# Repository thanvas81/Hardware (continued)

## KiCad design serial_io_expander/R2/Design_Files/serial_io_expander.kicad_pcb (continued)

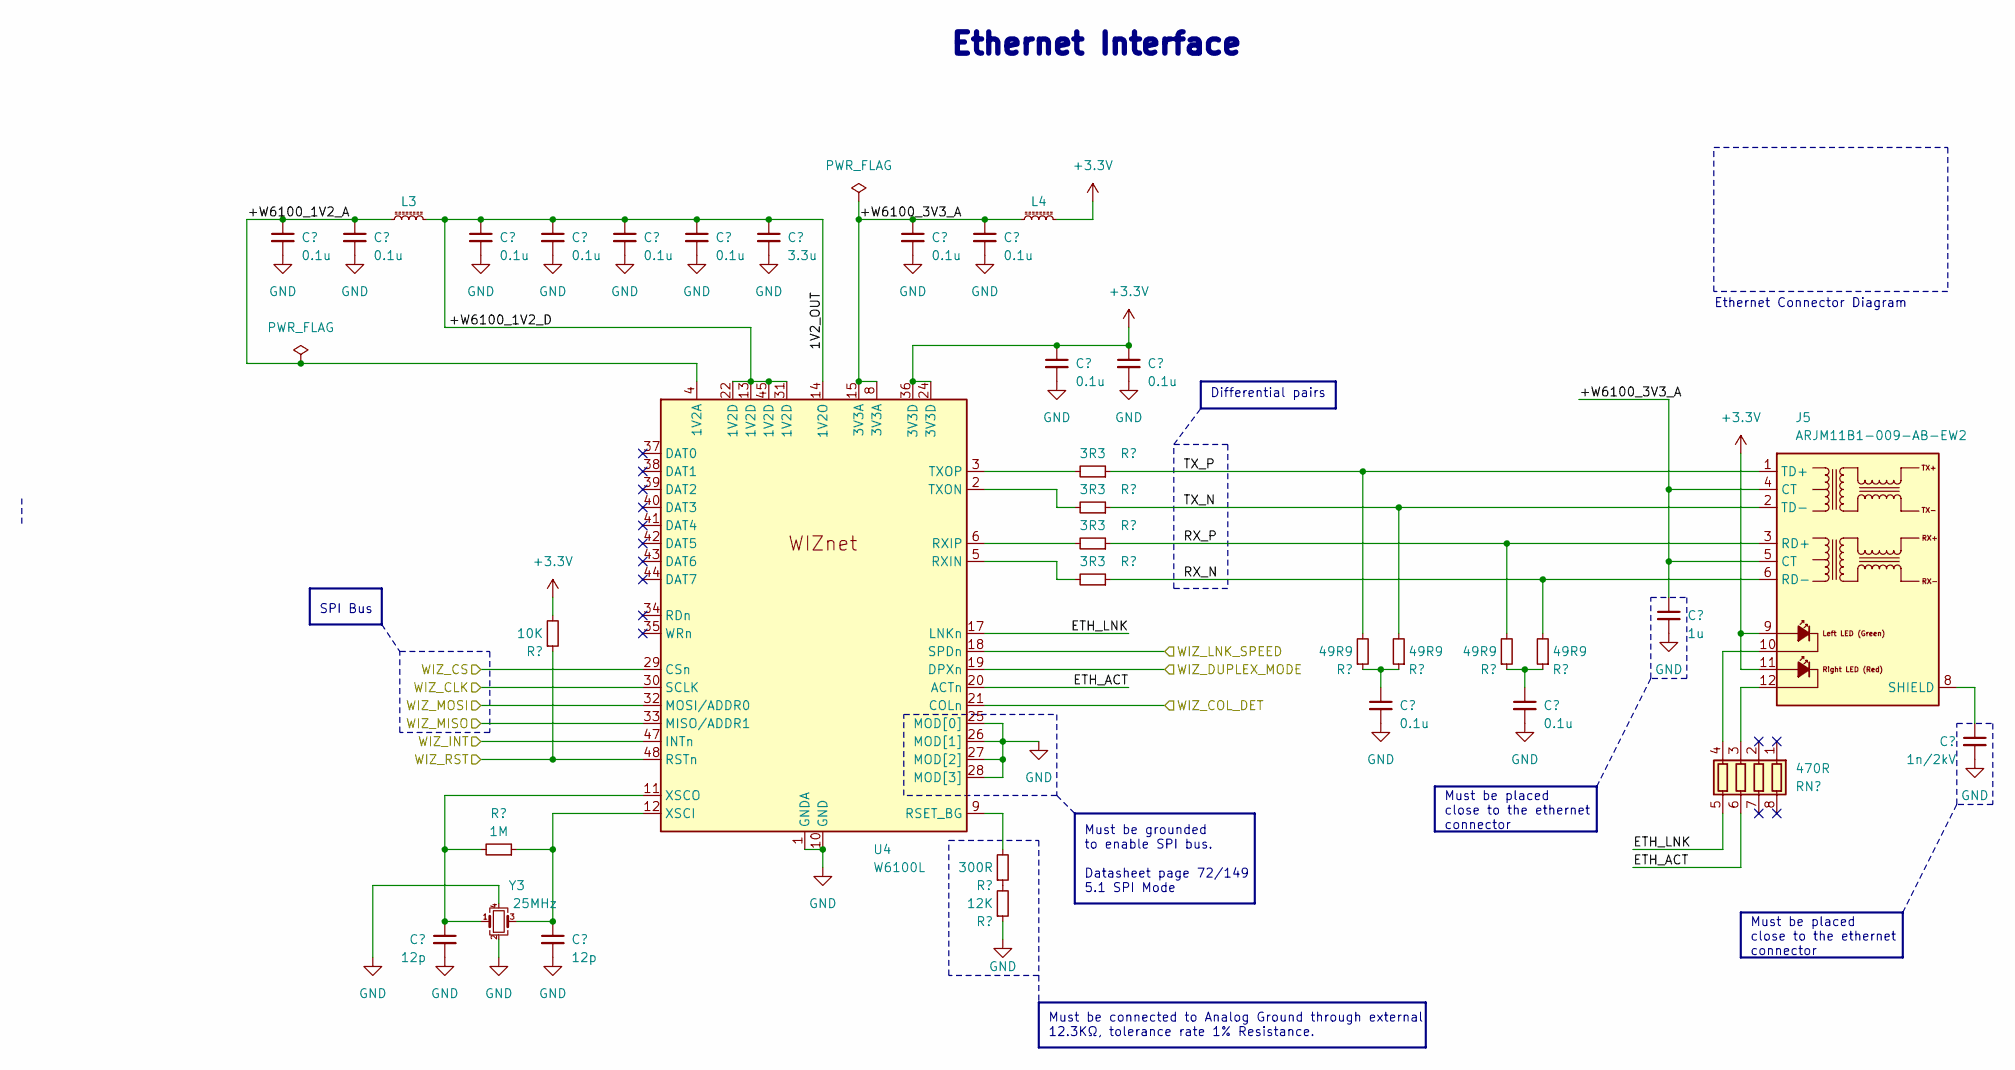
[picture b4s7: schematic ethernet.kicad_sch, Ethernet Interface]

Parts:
C31, C32, C34, C35, C37, C38, C40, C41, C42, C43, C44, C45: 0.1u; C_0603_1608Metric; PartkeeprID 50
C33, C36: 12p; C_0603_1608Metric; PartkeeprID 50
C39: 3.3u; C_0603_1608Metric
C46: 1u; C_0805_2012Metric; PartkeeprID 50
C47: 1n/2kV; C_1206_3216Metric; PartkeeprID 50
J5: ARJM11B1-009-AB-EW2; ARJM11B1-009-AB-EW2_Horizontal
L3, L4: L_Ferrite_Small; L_0603_1608Metric
R79: 1M; R_0402_1005Metric
R80: 10K; R_0603_1608Metric
R81: 300R; R_0402_1005Metric
R82: 12K; R_0402_1005Metric
R83, R84, R85, R86: 3R3; R_0402_1005Metric
R87, R88, R89, R90: 49R9; R_0402_1005Metric
RN1: 470R; R_Array_Concave_4x0603
U4: W6100L; LQFP-48_7x7mm_P0.5mm
Y3: 25MHz; Crystal_SMD_3225-4Pin_3.2x2.5mm

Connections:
/Ethernet/+W6100_1V2_A: C31.1, C32.1, L3.2, U4.4 (1V2A)
/Ethernet/+W6100_1V2_D: C34.1, C35.1, C37.1, C38.1, C39.1, L3.1, U4.13 (1V2D), U4.14 (1V2O), U4.22 (1V2D), U4.31 (1V2D), U4.45 (1V2D)
/Ethernet/+W6100_3V3_A: C40.1, C41.1, C46.1, J5.4 (CT), J5.5 (CT), L4.1, U4.8 (3V3A), U4.15 (3V3A)
/Ethernet/RX_N: J5.6 (RD-), R86.1, R90.2
/Ethernet/RX_P: J5.3 (RD+), R85.1, R89.2
/Ethernet/TX_N: J5.2 (TD-), R84.1, R88.2
/Ethernet/TX_P: J5.1 (TD+), R83.1, R87.2
/Ethernet/WIZ_CLK: U4.30 (SCLK); also elsewhere on the board
/Ethernet/WIZ_COL_DET: U4.21 (COLn); also elsewhere on the board
/Ethernet/WIZ_CS: U4.29 (CSn); also elsewhere on the board
/Ethernet/WIZ_DUPLEX_MODE: U4.19 (DPXn); also elsewhere on the board
/Ethernet/WIZ_INT: U4.47 (INTn); also elsewhere on the board
/Ethernet/WIZ_LNK_SPEED: U4.18 (SPDn); also elsewhere on the board
/Ethernet/WIZ_MISO: U4.33 (MISO/ADDR1); also elsewhere on the board
/Ethernet/WIZ_MOSI: U4.32 (MOSI/ADDR0); also elsewhere on the board
/Ethernet/WIZ_RST: R80.1, U4.48 (RSTn); also elsewhere on the board
GND: C31.2, C32.2, C33.2, C34.2, C35.2, C36.2, C37.2, C38.2, C39.2, C40.2, C41.2, C42.2, C43.2, C44.2, C45.2, C46.2, C47.2, R82.1, U4.1 (GNDA), U4.7 (GNDA), U4.10 (GND), U4.16 (GNDA), U4.23 (GND), U4.25 (MOD[0]), U4.26 (MOD[1]), U4.27 (MOD[2]), U4.28 (MOD[3]), U4.46 (GND), Y3.2, Y3.4; also elsewhere on the board
unnamed: C44.1, R87.1, R88.1
unnamed: C45.1, R89.1, R90.1
unnamed: C47.1, J5.8 (SHIELD)
unnamed: R81.1, R82.2
unnamed: R81.2, U4.9 (RSET_BG)
unnamed: R86.2, U4.5 (RXIN)
unnamed: R85.2, U4.6 (RXIP)
unnamed: R84.2, U4.2 (TXON)
unnamed: R83.2, U4.3 (TXOP)
unnamed: C36.1, R79.1, U4.12 (XSCI), Y3.3
unnamed: C33.1, R79.2, U4.11 (XSCO), Y3.1

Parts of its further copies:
RN8: 470R; R_Array_Concave_4x0603

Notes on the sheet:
${TITLE}
Must be connected to Analog Ground through external 12.3KΩ, tolerance rate 1% Resistance.
Must be placed close to the ethernet connector
SPI Bus
Must be grounded to enable SPI bus. Datasheet page 72/149 5.1 SPI Mode
Differential pairs
Ethernet Connector Diagram

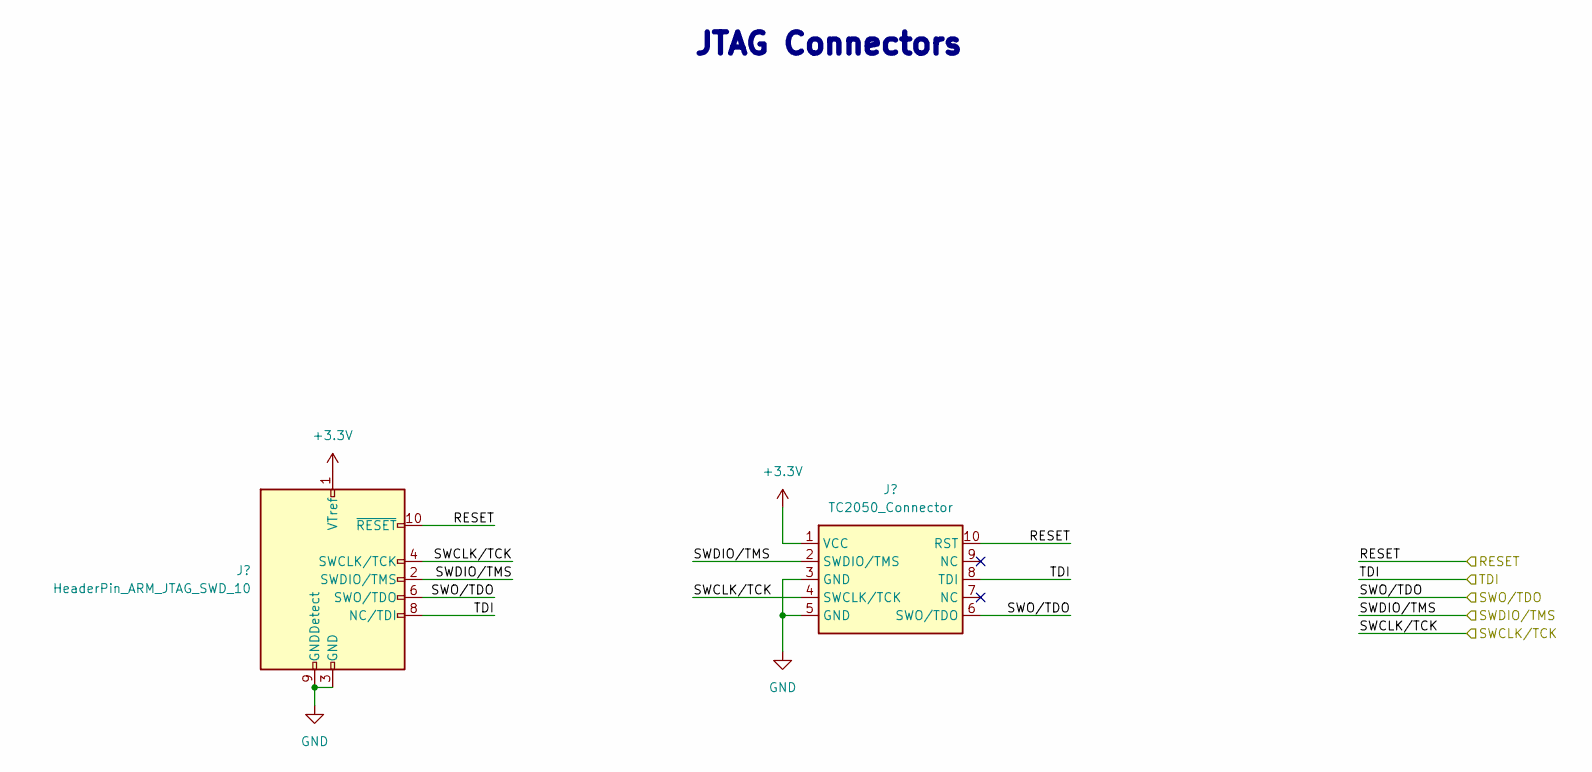
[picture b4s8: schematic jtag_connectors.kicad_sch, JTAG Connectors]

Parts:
J6: HeaderPin_ARM_JTAG_SWD_10; PinHeader_2x05_P2.54mm_Vertical
J7: TC2050_Connector; Tag-Connect_TC2050-IDC-NL_2x05_P1.27mm_Vertical

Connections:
/mcu/RESET: J6.10 (~RESET), J7.10 (RST); also elsewhere on the board
/mcu/SWCLK/TCK: J6.4 (SWCLK/TCK), J7.4 (SWCLK/TCK); also elsewhere on the board
/mcu/SWDIO/TMS: J6.2 (SWDIO/TMS), J7.2 (SWDIO/TMS); also elsewhere on the board
/mcu/SWO/TDO: J6.6 (SWO/TDO), J7.6 (SWO/TDO); also elsewhere on the board
/mcu/TDI: J6.8 (NC/TDI), J7.8 (TDI); also elsewhere on the board
GND: J6.3 (GND), J6.5 (GND), J6.9 (GNDDetect), J7.3 (GND), J7.5 (GND); also elsewhere on the board

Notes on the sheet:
${TITLE}

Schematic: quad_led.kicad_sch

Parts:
D47, D50, D53, D56: LED_Small_Filled; LED_0603_1608Metric
RN3: R_Pack04_Split; R_Array_Concave_4x0603
U7: PUMH11,115; SOT-363_SC-70-6

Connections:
/LED indicators/LED13: U7.2; also elsewhere on the board
/LED indicators/LED14: U7.5; also elsewhere on the board
GND: U7.1, U7.4; also elsewhere on the board

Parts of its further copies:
D24, D25, D26, D27, D28, D29, D30, D31, D32, D33, D34, D35, D36, D37, D38, D39, D40, D41, D42, D43, D48, D49: LED_Small_Filled; LED_0603_1608Metric
RN4, RN5, RN6, RN7, RN19: R_Pack04_Split; R_Array_Concave_4x0603
U8, U9, U10, U11, U12, U13, U14, U17, U18, U19, U20: PUMH11,115; SOT-363_SC-70-6

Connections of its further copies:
/LED indicators/LED1: U19.2; also elsewhere on the board
/LED indicators/LED2: U19.5; also elsewhere on the board
/LED indicators/LED3: U20.2; also elsewhere on the board
/LED indicators/LED4: U20.5; also elsewhere on the board
/LED indicators/LED5: U8.2; also elsewhere on the board
/LED indicators/LED6: U8.5; also elsewhere on the board
/LED indicators/LED7: U9.2; also elsewhere on the board
/LED indicators/LED8: U9.5; also elsewhere on the board
/LED indicators/LED9: U11.2; also elsewhere on the board
/LED indicators/LED10: U11.5; also elsewhere on the board
/LED indicators/LED11: U12.2; also elsewhere on the board
/LED indicators/LED12: U12.5; also elsewhere on the board
/LED indicators/LED15: U10.2; also elsewhere on the board
/LED indicators/LED16: U10.5; also elsewhere on the board
/LED indicators/LED17: U13.2; also elsewhere on the board
/LED indicators/LED18: U13.5; also elsewhere on the board
/LED indicators/LED19: U14.2; also elsewhere on the board
/LED indicators/LED20: U14.5; also elsewhere on the board
/LED indicators/LED21: U17.2; also elsewhere on the board
/LED indicators/LED22: U17.5; also elsewhere on the board
/LED indicators/LED23: U18.2; also elsewhere on the board
/LED indicators/LED24: U18.5; also elsewhere on the board
GND: U8.1, U8.4, U9.1, U9.4, U10.1, U10.4, U11.1, U11.4, U12.1, U12.4, U13.1, U13.4, U14.1, U14.4, U17.1, U17.4, U18.1, U18.4, U19.1, U19.4, U20.1, U20.4; also elsewhere on the board
unnamed: D24.1 (K), RN19.1 (R1.1)
unnamed: D25.1 (K), RN19.2 (R2.1)
unnamed: D32.1 (K), RN4.1 (R1.1)
unnamed: D33.1 (K), RN4.2 (R2.1)
unnamed: D34.1 (K), RN4.3 (R3.1)
unnamed: D35.1 (K), RN4.4 (R4.1)
unnamed: D36.1 (K), RN5.1 (R1.1)
unnamed: D37.1 (K), RN5.2 (R2.1)
unnamed: D38.1 (K), RN5.3 (R3.1)
unnamed: D39.1 (K), RN5.4 (R4.1)
unnamed: D40.1 (K), RN6.1 (R1.1)
unnamed: D41.1 (K), RN6.2 (R2.1)
unnamed: D42.1 (K), RN6.3 (R3.1)
unnamed: D43.1 (K), RN6.4 (R4.1)
unnamed: D48.1 (K), RN7.2 (R2.1)
unnamed: D49.1 (K), RN7.3 (R3.1)
unnamed: RN4.8 (R1.2), U11.6
unnamed: RN4.7 (R2.2), U11.3
unnamed: RN4.6 (R3.2), U12.6
unnamed: RN4.5 (R4.2), U12.3
unnamed: RN5.8 (R1.2), U13.6
unnamed: RN5.7 (R2.2), U13.3
unnamed: RN5.6 (R3.2), U14.6
unnamed: RN5.5 (R4.2), U14.3
unnamed: RN6.8 (R1.2), U17.6
unnamed: RN6.7 (R2.2), U17.3
unnamed: RN6.6 (R3.2), U18.6
unnamed: RN6.5 (R4.2), U18.3
unnamed: RN7.8 (R1.2), U19.6
unnamed: RN7.7 (R2.2), U19.3
unnamed: RN7.6 (R3.2), U20.6
unnamed: RN7.5 (R4.2), U20.3
unnamed: RN19.8 (R1.2), U8.6
unnamed: RN19.7 (R2.2), U8.3
unnamed: RN19.6 (R3.2), U9.6
unnamed: RN19.5 (R4.2), U9.3

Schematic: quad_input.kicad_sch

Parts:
D8, D13, D18, D23: TBAW56,LM; SOT-23
RN9: 120K; R_Array_Concave_4x0603
RN10: 47K; R_Array_Concave_4x0603
U5, U6: PUMH11,115; SOT-363_SC-70-6

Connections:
/digital_inputs/COLLECTOR1: U6.3; also elsewhere on the board
/digital_inputs/COLLECTOR2: U6.6; also elsewhere on the board
/digital_inputs/COLLECTOR3: U5.6; also elsewhere on the board
/digital_inputs/COLLECTOR4: U5.3; also elsewhere on the board
/digital_inputs/IN1: RN9.8 (R1.2), RN10.5 (R4.2); also elsewhere on the board
/digital_inputs/IN2: RN9.7 (R2.2), RN10.6 (R3.2); also elsewhere on the board
/digital_inputs/IN3: RN9.6 (R3.2), RN10.7 (R2.2); also elsewhere on the board
/digital_inputs/IN4: RN9.5 (R4.2), RN10.8 (R1.2); also elsewhere on the board
/digital_inputs/quad_input1/+PULLUP: D8.3 (A), D13.3 (A); also elsewhere on the board
GND: D18.3 (A), D23.3 (A), U5.1, U5.4, U6.1, U6.4; also elsewhere on the board
unnamed: D23.1 (K), RN9.1 (R1.1), U5.5
unnamed: D23.2 (K), RN9.2 (R2.1), U5.2
unnamed: D18.2 (K), RN9.3 (R3.1), U6.2
unnamed: D18.1 (K), RN9.4 (R4.1), U6.5
unnamed: D13.2 (K), RN10.1 (R1.1)
unnamed: D13.1 (K), RN10.2 (R2.1)
unnamed: D8.2 (K), RN10.3 (R3.1)
unnamed: D8.1 (K), RN10.4 (R4.1)

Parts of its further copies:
D3, D4, D6, D7, D9, D10, D11, D12, D14, D15, D16, D17, D19, D20, D21, D22: TBAW56,LM; SOT-23
RN11, RN13, RN15, RN17: 47K; R_Array_Concave_4x0603
RN12, RN14, RN16, RN18: 120K; R_Array_Concave_4x0603
U15, U16, U21, U22, U27, U28, U33, U34: PUMH11,115; SOT-363_SC-70-6

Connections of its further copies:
/digital_inputs/COLLECTOR5: U16.3; also elsewhere on the board
/digital_inputs/COLLECTOR6: U16.6; also elsewhere on the board
/digital_inputs/COLLECTOR7: U15.6; also elsewhere on the board
/digital_inputs/COLLECTOR8: U15.3; also elsewhere on the board
/digital_inputs/COLLECTOR9: U22.3; also elsewhere on the board
/digital_inputs/COLLECTOR10: U22.6; also elsewhere on the board
/digital_inputs/COLLECTOR11: U21.6; also elsewhere on the board
/digital_inputs/COLLECTOR12: U21.3; also elsewhere on the board
/digital_inputs/COLLECTOR13: U34.3; also elsewhere on the board
/digital_inputs/COLLECTOR14: U34.6; also elsewhere on the board
/digital_inputs/COLLECTOR15: U33.6; also elsewhere on the board
/digital_inputs/COLLECTOR16: U33.3; also elsewhere on the board
/digital_inputs/COLLECTOR17: U28.3; also elsewhere on the board
/digital_inputs/COLLECTOR18: U28.6; also elsewhere on the board
/digital_inputs/COLLECTOR19: U27.6; also elsewhere on the board
/digital_inputs/COLLECTOR20: U27.3; also elsewhere on the board
/digital_inputs/IN5: RN11.5 (R4.2), RN12.8 (R1.2); also elsewhere on the board
/digital_inputs/IN6: RN11.6 (R3.2), RN12.7 (R2.2); also elsewhere on the board
/digital_inputs/IN7: RN11.7 (R2.2), RN12.6 (R3.2); also elsewhere on the board
/digital_inputs/IN8: RN11.8 (R1.2), RN12.5 (R4.2); also elsewhere on the board
/digital_inputs/IN9: RN13.5 (R4.2), RN14.8 (R1.2); also elsewhere on the board
/digital_inputs/IN10: RN13.6 (R3.2), RN14.7 (R2.2); also elsewhere on the board
/digital_inputs/IN11: RN13.7 (R2.2), RN14.6 (R3.2); also elsewhere on the board
/digital_inputs/IN12: RN13.8 (R1.2), RN14.5 (R4.2); also elsewhere on the board
/digital_inputs/IN13: RN17.5 (R4.2), RN18.8 (R1.2); also elsewhere on the board
/digital_inputs/IN14: RN17.6 (R3.2), RN18.7 (R2.2); also elsewhere on the board
/digital_inputs/IN15: RN17.7 (R2.2), RN18.6 (R3.2); also elsewhere on the board
/digital_inputs/IN16: RN17.8 (R1.2), RN18.5 (R4.2); also elsewhere on the board
/digital_inputs/IN17: RN15.5 (R4.2), RN16.8 (R1.2); also elsewhere on the board
/digital_inputs/IN18: RN15.6 (R3.2), RN16.7 (R2.2); also elsewhere on the board
/digital_inputs/IN19: RN15.7 (R2.2), RN16.6 (R3.2); also elsewhere on the board
/digital_inputs/IN20: RN15.8 (R1.2), RN16.5 (R4.2); also elsewhere on the board
/digital_inputs/quad_input1/+PULLUP: D3.3 (A), D4.3 (A), D6.3 (A), D7.3 (A), D9.3 (A), D10.3 (A), D11.3 (A), D12.3 (A); also elsewhere on the board
GND: D14.3 (A), D15.3 (A), D16.3 (A), D17.3 (A), D19.3 (A), D20.3 (A), D21.3 (A), D22.3 (A), U15.1, U15.4, U16.1, U16.4, U21.1, U21.4, U22.1, U22.4, U27.1, U27.4, U28.1, U28.4, U33.1, U33.4, U34.1, U34.4; also elsewhere on the board
unnamed: D9.2 (K), RN11.1 (R1.1)
unnamed: D9.1 (K), RN11.2 (R2.1)
unnamed: D3.2 (K), RN11.3 (R3.1)
unnamed: D3.1 (K), RN11.4 (R4.1)
unnamed: D19.1 (K), RN12.1 (R1.1), U15.5
unnamed: D19.2 (K), RN12.2 (R2.1), U15.2
unnamed: D14.2 (K), RN12.3 (R3.1), U16.2
unnamed: D14.1 (K), RN12.4 (R4.1), U16.5
unnamed: D10.2 (K), RN13.1 (R1.1)
unnamed: D10.1 (K), RN13.2 (R2.1)
unnamed: D4.2 (K), RN13.3 (R3.1)
unnamed: D4.1 (K), RN13.4 (R4.1)
unnamed: D20.1 (K), RN14.1 (R1.1), U21.5
unnamed: D20.2 (K), RN14.2 (R2.1), U21.2
unnamed: D15.2 (K), RN14.3 (R3.1), U22.2
unnamed: D15.1 (K), RN14.4 (R4.1), U22.5
unnamed: D11.2 (K), RN15.1 (R1.1)
unnamed: D11.1 (K), RN15.2 (R2.1)
unnamed: D6.2 (K), RN15.3 (R3.1)
unnamed: D6.1 (K), RN15.4 (R4.1)
unnamed: D21.1 (K), RN16.1 (R1.1), U27.5
unnamed: D21.2 (K), RN16.2 (R2.1), U27.2
unnamed: D16.2 (K), RN16.3 (R3.1), U28.2
unnamed: D16.1 (K), RN16.4 (R4.1), U28.5
unnamed: D12.2 (K), RN17.1 (R1.1)
unnamed: D12.1 (K), RN17.2 (R2.1)
unnamed: D7.2 (K), RN17.3 (R3.1)
unnamed: D7.1 (K), RN17.4 (R4.1)
unnamed: D22.1 (K), RN18.1 (R1.1), U33.5
unnamed: D22.2 (K), RN18.2 (R2.1), U33.2
unnamed: D17.2 (K), RN18.3 (R3.1), U34.2
unnamed: D17.1 (K), RN18.4 (R4.1), U34.5

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
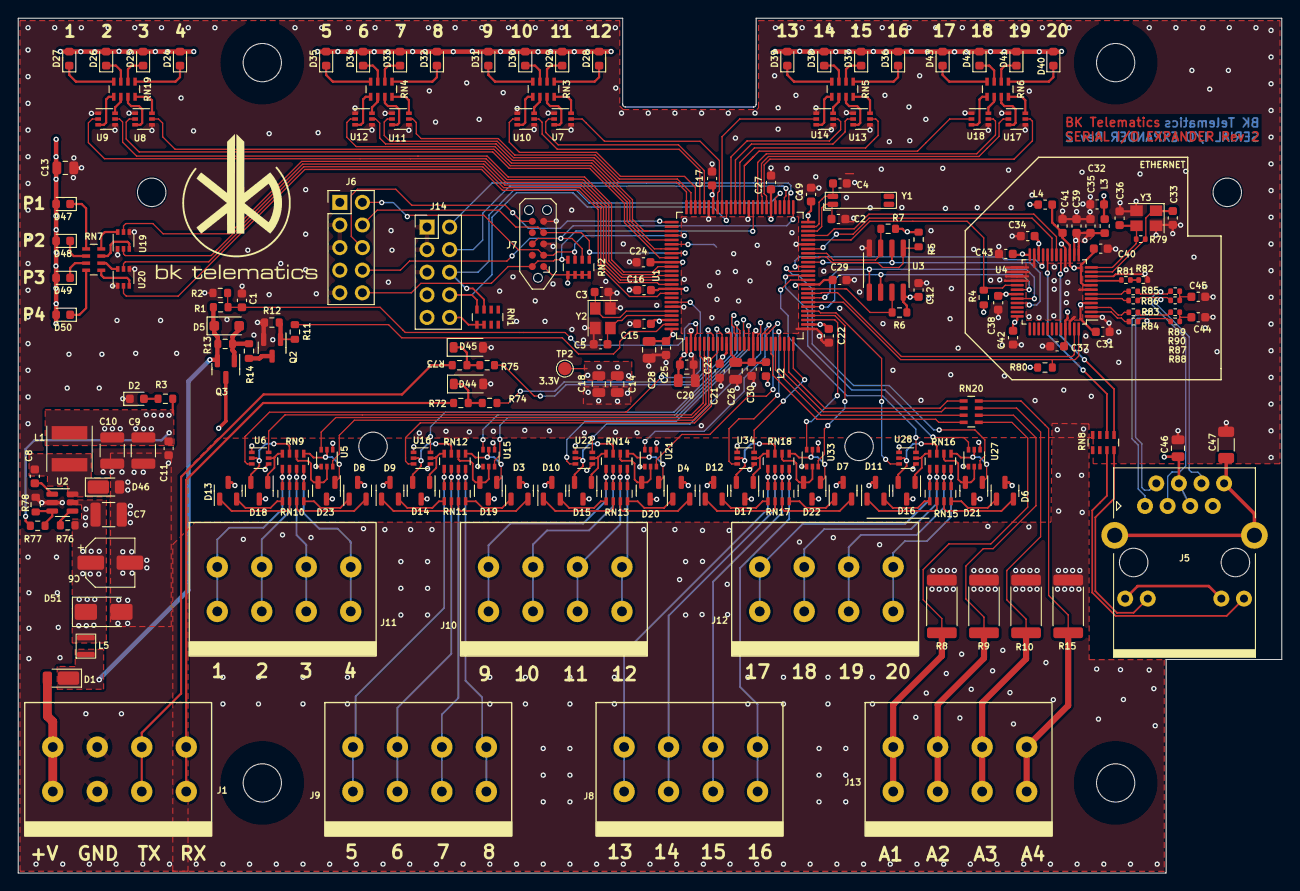
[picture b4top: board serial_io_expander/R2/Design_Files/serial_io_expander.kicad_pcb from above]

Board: 4 copper layers, 142.0 x 96.1 mm, 209 parts (1 on the bottom side), 232 nets.

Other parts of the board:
C12, C15, C16, C17, C19, C21, C22, C23, C24, C25, C27, C29, C30: 0.1u; C_0603_1608Metric
C14, C20, C26, C28: 4.7u; C_0805_2012Metric
C18: 10u; C_0805_2012Metric
L2: 10uH; L_0603_1608Metric
U3: AT25SF321B-SSHB-X; SOIC-8_3.9x4.9mm_P1.27mm

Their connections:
/Ethernet/WIZ_CLK: U3.6 (SCK); also elsewhere on the board
/Ethernet/WIZ_MISO: U3.2 (SO/IO1); also elsewhere on the board
/Ethernet/WIZ_MOSI: U3.5 (SI/IO0); also elsewhere on the board
/NOR Flash/FLASH_MEM_CS: U3.1 (~CS); also elsewhere on the board
/NOR Flash/FLASH_MEM_HOLD: U3.7 (~HOLD/IO3); also elsewhere on the board
/NOR Flash/FLASH_MEM_WP: U3.3 (~WP/IO2); also elsewhere on the board
/mcu/MCU Supply/+VDDCORE: C24.1, C26.1, C27.1, C29.1, C30.1, L2.2; also elsewhere on the board
/mcu/MCU Supply/+VDDPLL: C25.1, C28.1, L2.1; also elsewhere on the board
GND: C12.2, C14.2, C15.2, C16.2, C17.2, C18.2, C19.2, C20.2, C21.2, C22.2, C23.2, C24.2, C25.2, C26.2, C27.2, C28.2, C29.2, C30.2, U3.4 (GND); also elsewhere on the board

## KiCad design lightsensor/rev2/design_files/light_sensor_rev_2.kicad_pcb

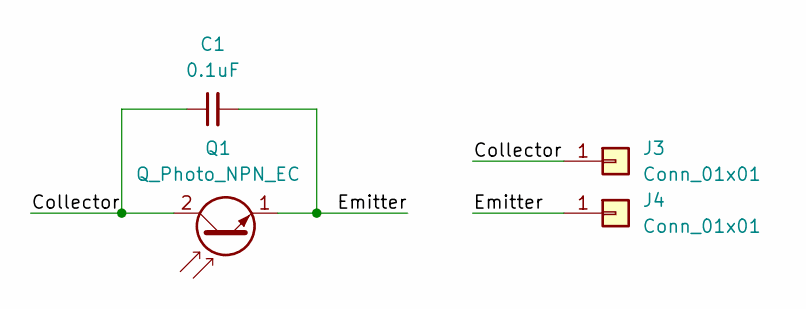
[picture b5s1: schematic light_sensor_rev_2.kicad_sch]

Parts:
C1: 0.1uF; C_0603_1608Metric
J3, J4: Conn_01x01; pad_smd_3x4
Q1: Q_Photo_NPN_EC; SFH-3410

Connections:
/Collector: C1.1, J3.1, Q1.2 (C)
/Emitter: C1.2, J4.1, Q1.1 (E)

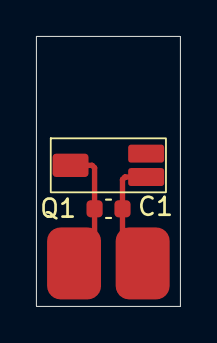
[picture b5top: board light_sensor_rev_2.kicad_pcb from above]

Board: 2 copper layers, 8.0 x 15.0 mm, 4 parts (0 on the bottom side), 2 nets.

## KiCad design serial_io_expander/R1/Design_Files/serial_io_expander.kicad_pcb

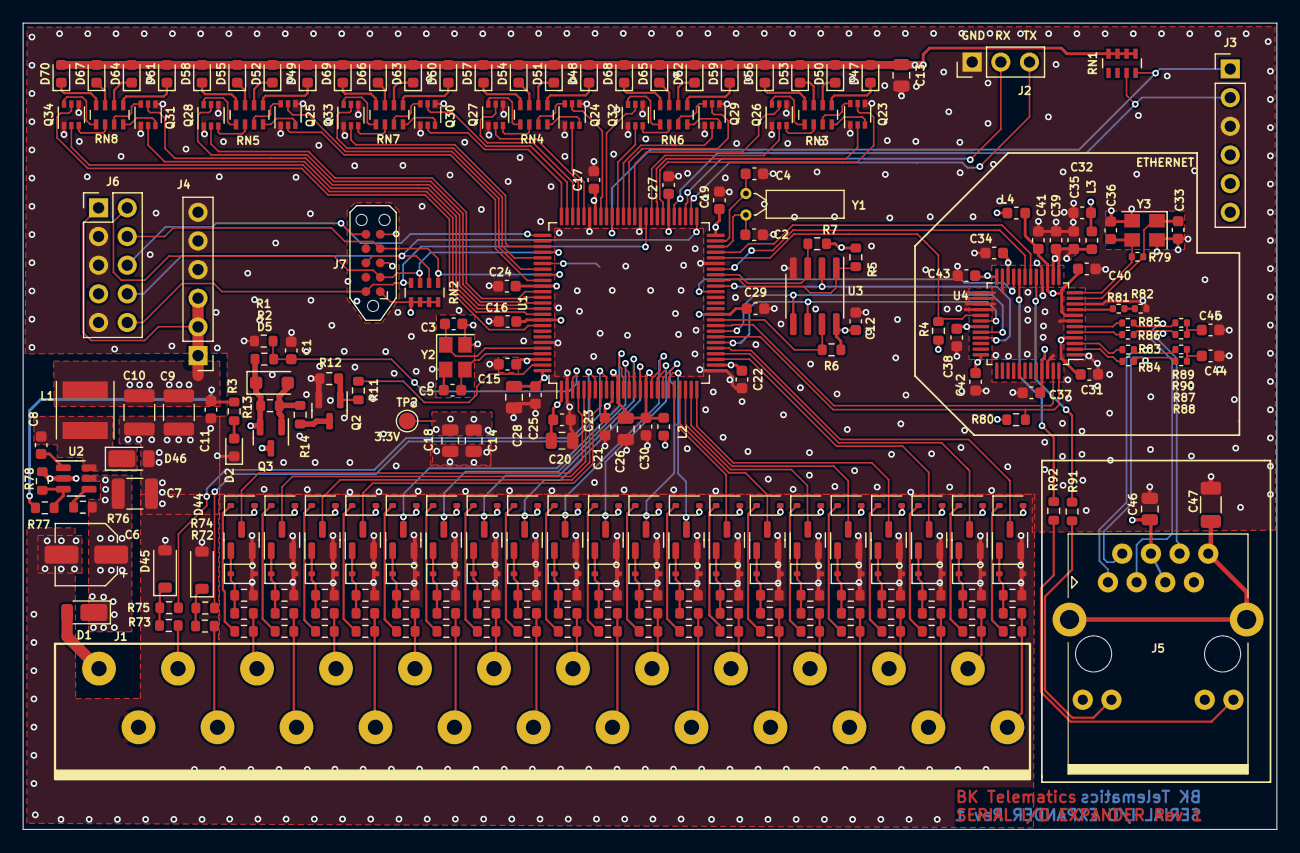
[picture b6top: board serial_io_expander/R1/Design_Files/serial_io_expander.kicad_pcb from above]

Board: 4 copper layers, 111.1 x 71.4 mm, 271 parts (1 on the bottom side), 223 nets.

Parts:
C1, C8, C11, C12, C15, C16, C17, C19, C21, C22, C23, C24, C25, C27, C29, C30, C31, C32, C34, C35, C37, C38, C40, C41, C42, C43, C44, C45: 0.1u; C_0603_1608Metric
C2, C3, C4, C5: C_0603_1608Metric
C6: 10u; CP_Elec_5x5.3
C7: 2.2u; C_1210_3225Metric
C9, C10: 22u; C_1210_3225Metric
C13, C18: 10u; C_0805_2012Metric
C14, C20, C26, C28: 4.7u; C_0805_2012Metric
C33, C36: 12p; C_0603_1608Metric
C39: 3.3u; C_0603_1608Metric
C46: 1u; C_0805_2012Metric
C47: 1n/2kV; C_1206_3216Metric
D1, D46: SBR3U60P1Q-7; D_PowerDI-123
D2, D47, D48, D49, D50, D51, D52, D53, D54, D55, D56, D57, D58, D59, D60, D61, D62, D63, D64, D65, D66, D67, D68, D69, D70: LED_Small_Filled; LED_0603_1608Metric
D3, D4, D6, D7, D8, D9, D10, D11, D12, D13, D14, D15, D16, D17, D18, D19, D20, D21, D22, D23, D24, D25, D26, D27, D28, D29, D30, D31, D32, D33, D34, D35, D36, D37, D38, D39, D40, D41, D42, D43: 1N4148WX-TP; D_SOD-323
D5: 8.2V; D_SOD-123F
D44, D45: 3V; D_SOD-123
J1: Conn_01x24; TerminalBlock_TE_1-2834011-x(24P-merged)
J2: Conn_01x03; PinHeader_1x03_P2.54mm_Vertical
J3, J4: Conn_01x06; PinHeader_1x06_P2.54mm_Vertical
J5: ARJM11B1-009-AB-EW2; ARJM11B1-009-AB-EW2_Horizontal
J6: HeaderPin_ARM_JTAG_SWD_10; PinHeader_2x05_P2.54mm_Vertical
J7: TC2050_Connector; Tag-Connect_TC2050-IDC-NL_2x05_P1.27mm_Vertical
L1: 22uH; L_Taiyo-Yuden_NR-50xx
L2: 10uH; L_0603_1608Metric
L3, L4: L_Ferrite_Small; L_0603_1608Metric
Q1, Q2, Q4, Q5, Q6, Q7, Q8, Q9, Q10, Q11, Q12, Q13, Q14, Q15, Q16, Q17, Q18, Q19, Q20, Q21, Q22: MMBT3904; SOT-23
Q3: BSS84; SOT-23
Q23, Q24, Q25, Q26, Q27, Q28, Q29, Q30, Q31, Q32, Q33, Q34: MUN5211DW1; SOT-363_SC-70-6
R1, R4, R5, R6, R7, R76: 100K; R_0603_1608Metric
R2, R10, R11, R12, R13, R14, R17, R20, R23, R26, R29, R32, R35, R38, R41, R44, R47, R50, R53, R56, R59, R62, R65, R68, R71, R78, R80: 10K; R_0603_1608Metric
R3, R91, R92: 470R; R_0603_1608Metric
R8, R15, R18, R21, R24, R27, R30, R33, R36, R39, R42, R45, R48, R51, R54, R57, R60, R63, R66, R69: 47K; R_0603_1608Metric
R9, R16, R19, R22, R25, R28, R31, R34, R37, R40, R43, R46, R49, R52, R55, R58, R61, R64, R67, R70: 150K; R_0603_1608Metric
R72, R73: 4K7; R_0603_1608Metric
R74, R75: 100R; R_0603_1608Metric
R77: 33K; R_0603_1608Metric
R79: 1M; R_0402_1005Metric
R81: 300R; R_0402_1005Metric
R82: 12K; R_0402_1005Metric
R83, R84, R85, R86: 3R3; R_0402_1005Metric
R87, R88, R89, R90: 49R9; R_0402_1005Metric
RN1: 4K7; R_Array_Concave_4x0603
RN2: 100K; R_Array_Concave_4x0603
RN3, RN4, RN5, RN6, RN7, RN8: R_Pack04_Split; R_Array_Concave_4x0603
TP1, TP2: TestPoint; TestPoint_Pad_D1.5mm
U1: ATSAM4S4C; LQFP-100_14x14mm_P0.5mm
U2: LV2862x; SOT-23-6
U3: AT25SF321B-SSHB-X; SOIC-8_3.9x4.9mm_P1.27mm
U4: W6100L; LQFP-48_7x7mm_P0.5mm
Y1: 32.768KHz; Crystal_C26-LF_D2.1mm_L6.5mm_Horizontal
Y2: 12MHz; Crystal_SMD_Abracon_ABM8G-4Pin_3.2x2.5mm
Y3: 25MHz; Crystal_SMD_3225-4Pin_3.2x2.5mm

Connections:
+3.3V: C9.1, C10.1, C11.1, C12.1, C13.1, C14.1, C15.1, C16.1, C17.1, C18.1, C19.1, C20.1, C21.1, C22.1, C23.1, C42.1, C43.1, D47.2 (A), D48.2 (A), D49.2 (A), D50.2 (A), D51.2 (A), D52.2 (A), D53.2 (A), D54.2 (A), D55.2 (A), D56.2 (A), D57.2 (A), D58.2 (A), D59.2 (A), D60.2 (A), D61.2 (A), D62.2 (A), D63.2 (A), D64.2 (A), D65.2 (A), D66.2 (A), D67.2 (A), D68.2 (A), D69.2 (A), D70.2 (A), J4.1, J4.2, J4.3, J5.9, J5.11, J6.1 (VTref), J7.1 (VCC), L1.2, L4.2, R3.2, R4.1, R5.1, R6.1, R7.1, R77.2, R80.2, RN1.5 (R4.2), RN1.6 (R3.2), RN1.7 (R2.2), RN1.8 (R1.2), RN2.5 (R4.2), RN2.6 (R3.2), RN2.7 (R2.2), RN2.8 (R1.2), TP2.1, U1.1 (ADVREF), U1.10 (VDDIN), U1.27 (VDDIO), U1.50 (VDDIO), U1.69 (VDDIO), U1.91 (VDDIO), U1.98 (VDDIO), U3.8 (VCC), U4.24 (3V3D), U4.36 (3V3D)
+VIN: C6.1, C7.1, D1.1 (K), D5.1 (K), Q3.2 (S), R1.1, R13.2, R76.2, U2.5 (VIN)
/+PWR: D1.2 (A), J1.24
/Ethernet/+W6100_1V2_A: C31.1, C32.1, L3.2, U4.4 (1V2A)
/Ethernet/+W6100_1V2_D: C34.1, C35.1, C37.1, C38.1, C39.1, L3.1, U4.13 (1V2D), U4.14 (1V2O), U4.22 (1V2D), U4.31 (1V2D), U4.45 (1V2D)
/Ethernet/+W6100_3V3_A: C40.1, C41.1, C46.1, J5.4 (CT), J5.5 (CT), L4.1, U4.8 (3V3A), U4.15 (3V3A)
/Ethernet/ETH_ACT: R92.1, U4.20 (ACTn)
/Ethernet/ETH_LNK: R91.1, U4.17 (LNKn)
/Ethernet/RX_N: J5.6 (RD-), R86.1, R90.2
/Ethernet/RX_P: J5.3 (RD+), R85.1, R89.2
/Ethernet/TX_N: J5.2 (TD-), R84.1, R88.2
/Ethernet/TX_P: J5.1 (TD+), R83.1, R87.2
/Ethernet/WIZ_CLK: U1.31 (PA14), U3.6 (SCK), U4.30 (SCLK)
/Ethernet/WIZ_COL_DET: U1.40 (PC3), U4.21 (COLn)
/Ethernet/WIZ_CS: R4.2, U1.46 (PA9), U4.29 (CSn)
/Ethernet/WIZ_DUPLEX_MODE: U1.44 (PA10), U4.19 (DPXn)
/Ethernet/WIZ_INT: U1.34 (PA24), U4.47 (INTn)
/Ethernet/WIZ_LNK_SPEED: U1.47 (PC1), U4.18 (SPDn)
/Ethernet/WIZ_MISO: U1.41 (PA12), U3.2 (SO/IO1), U4.33 (MISO/ADDR1)
/Ethernet/WIZ_MOSI: U1.33 (PA13), U3.5 (SI/IO0), U4.32 (MOSI/ADDR0)
/Ethernet/WIZ_RST: R80.1, U1.32 (PC6), U4.48 (RSTn)
/LED indicators/LED1: Q23.5 (B1), U1.57 (PA27)
/LED indicators/LED2: Q23.2 (B2), U1.58 (PC8)
/LED indicators/LED3: Q26.5 (B1), U1.62 (PC9)
/LED indicators/LED4: Q26.2 (B2), U1.59 (PA28)
/LED indicators/LED5: Q29.5 (B1), U1.63 (PA29)
/LED indicators/LED6: Q29.2 (B2), U1.64 (PA30)
/LED indicators/LED7: Q32.5 (B1), U1.67 (PA2)
/LED indicators/LED8: Q32.2 (B2), U1.65 (PC10)
/LED indicators/LED9: Q24.5 (B1), U1.68 (PC11)
/LED indicators/LED10: Q24.2 (B2), U1.71 (PC14)
/LED indicators/LED11: Q27.5 (B1), U1.73 (PC16)
/LED indicators/LED12: Q27.2 (B2), U1.72 (PA1)
/LED indicators/LED13: Q30.5 (B1), U1.74 (PA0)
/LED indicators/LED14: Q30.2 (B2), U1.75 (PC17)
/LED indicators/LED15: Q33.5 (B1), U1.80 (PC19)
/LED indicators/LED16: Q33.2 (B2), U1.78 (PC18)
/LED indicators/LED17: Q25.5 (B1), U1.82 (PC20)
/LED indicators/LED18: Q25.2 (B2), U1.84 (PC21)
/LED indicators/LED19: Q28.5 (B1), U1.87 (PB12/ERASE)
/LED indicators/LED20: Q28.2 (B2), U1.86 (PC22)
/LED indicators/LED21: Q31.5 (B1), U1.88 (PB10/DDM)
/LED indicators/LED22: Q31.2 (B2), U1.89 (PB11/DDP)
/LED indicators/LED23: Q34.5 (B1), U1.92 (PC24)
/LED indicators/LED24: Q34.2 (B2), U1.90 (PC23)
/NOR Flash/FLASH_MEM_CS: R5.2, U1.42 (PA11), U3.1 (~CS)
/NOR Flash/FLASH_MEM_HOLD: R6.2, U1.35 (PC5), U3.7 (~HOLD/IO3)
/NOR Flash/FLASH_MEM_WP: R7.2, U1.43 (PC2), U3.3 (~WP/IO2)
/SERIAL_RX: J1.22, R73.1
/SERIAL_TX: J1.21, R72.1
/VIN_MEAS: C1.1, R1.2, R2.1, U1.3 (PB0/AD4)
/digital_inputs/COLLECTOR1: Q1.3 (C), U1.4 (PC29/AD13)
/digital_inputs/COLLECTOR2: Q4.3 (C), U1.5 (PB1/AD5)
/digital_inputs/COLLECTOR3: Q5.3 (C), U1.6 (PC30/AD14)
/digital_inputs/COLLECTOR4: Q6.3 (C), U1.8 (PC31)
/digital_inputs/COLLECTOR5: Q7.3 (C), U1.12 (PA17/AD0)
/digital_inputs/COLLECTOR6: Q8.3 (C), U1.13 (PC26)
/digital_inputs/COLLECTOR7: Q9.3 (C), U1.14 (PA18/AD1)
/digital_inputs/COLLECTOR8: Q11.3 (C), U1.15 (PA21/AD8)
/digital_inputs/COLLECTOR9: Q12.3 (C), U1.17 (PC27)
/digital_inputs/COLLECTOR10: Q13.3 (C), U1.18 (PA19/AD2)
/digital_inputs/COLLECTOR11: Q14.3 (C), U1.19 (PC15/AD11)
/digital_inputs/COLLECTOR12: Q15.3 (C), U1.20 (PA22/AD9)
/digital_inputs/COLLECTOR13: Q16.3 (C), U1.21 (PC13/AD10)
/digital_inputs/COLLECTOR14: Q17.3 (C), U1.22 (PA23)
/digital_inputs/COLLECTOR15: Q19.3 (C), U1.23 (PC12/AD12)
/digital_inputs/COLLECTOR16: Q20.3 (C), U1.24 (PA20/AD3)
/digital_inputs/COLLECTOR17: Q21.3 (C), U1.25 (PC0)
/digital_inputs/COLLECTOR18: Q22.3 (C), U1.28 (PA16)
/digital_inputs/COLLECTOR19: Q10.3 (C), U1.29 (PC7)
/digital_inputs/COLLECTOR20: Q18.3 (C), U1.30 (PA15)
/digital_inputs/IN1: J1.20, R8.1, R9.1
/digital_inputs/IN2: J1.19, R15.1, R16.1
/digital_inputs/IN3: J1.18, R18.1, R19.1
/digital_inputs/IN4: J1.17, R21.1, R22.1
/digital_inputs/IN5: J1.16, R24.1, R25.1
/digital_inputs/IN6: J1.15, R27.1, R28.1
/digital_inputs/IN7: J1.14, R30.1, R31.1
/digital_inputs/IN8: J1.13, R36.1, R37.1
/digital_inputs/IN9: J1.12, R39.1, R40.1
/digital_inputs/IN10: J1.11, R42.1, R43.1
/digital_inputs/IN11: J1.10, R45.1, R46.1
/digital_inputs/IN12: J1.9, R48.1, R49.1
/digital_inputs/IN13: J1.8, R51.1, R52.1
/digital_inputs/IN14: J1.7, R54.1, R55.1
/digital_inputs/IN15: J1.6, R60.1, R61.1
/digital_inputs/IN16: J1.5, R63.1, R64.1
/digital_inputs/IN17: J1.4, R66.1, R67.1
/digital_inputs/IN18: J1.3, R69.1, R70.1
/digital_inputs/IN19: J1.2, R33.1, R34.1
/digital_inputs/IN20: J1.1, R57.1, R58.1
/digital_inputs/PULLUP_EN: R11.2, U1.99 (PB14/DAC1)
/digital_inputs/input1/PULLUP: D3.2 (A), D6.2 (A), D8.2 (A), D10.2 (A), D12.2 (A), D14.2 (A), D16.2 (A), D18.2 (A), D20.2 (A), D22.2 (A), D24.2 (A), D26.2 (A), D28.2 (A), D30.2 (A), D32.2 (A), D34.2 (A), D36.2 (A), D38.2 (A), D40.2 (A), D42.2 (A), Q3.3 (D)
/mcu/DEBUG_RX: J2.2, U1.53 (PA5)
/mcu/DEBUG_TX: J2.3, U1.52 (PA6)
/mcu/ERASE: TP1.1, U1.81 (PA31)
/mcu/MCU Supply/+VDDCORE: C24.1, C26.1, C27.1, C29.1, C30.1, L2.2, U1.11 (VDDOUT), U1.16 (VDDCORE), U1.36 (VDDCORE), U1.56 (VDDCORE), U1.85 (VDDCORE)
/mcu/MCU Supply/+VDDPLL: C25.1, C28.1, L2.1, U1.100 (VDDPLL)
/mcu/MCU_RX: R75.2, U1.7 (PB2/AD6)
/mcu/MCU_TX: R74.2, U1.9 (PB3/AD7)
/mcu/RESET: J6.10 (~RESET), J7.10 (RST), RN2.4 (R4.1), U1.60 (NRST)
/mcu/SWCLK/TCK: J6.4 (SWDCLK/TCK), J7.4 (SWCLK/TCK), RN2.1 (R1.1), U1.83 (PB7/TCK/SWCLK)
/mcu/SWDIO/TMS: J6.2 (SWDIO/TMS), J7.2 (SWDIO/TMS), RN2.3 (R3.1), U1.79 (PB6/TMS/SWDIO)
/mcu/SWO/TDO: J6.6 (SWO/TDO), J7.6 (SWO/TDO), U1.76 (PB5/TDO/TRACESWO)
/mcu/TDI: J6.8 (NC/TDI), J7.8 (TDI), RN2.2 (R2.1), U1.51 (TDI/PB4)
/mcu/TWI_SCL: J3.2, RN1.3 (R3.1), U1.55 (PA4)
/mcu/TWI_SDA: J3.1, RN1.4 (R4.1), U1.66 (PA3)
/mcu/XIN: C5.1, U1.97 (PB9/PGMCK/XIN), Y2.3
/mcu/XIN32: C4.1, U1.49 (PA7/XIN32), Y1.2
/mcu/XOUT: C3.1, U1.96 (PB8/XOUT), Y2.1
/mcu/XOUT32: C2.1, U1.48 (PA8/XOUT32), Y1.1
/power supply/SW: C8.2, D46.1 (K), L1.1, U2.6 (SW)
GND: C1.2, C2.2, C3.2, C4.2, C5.2, C6.2, C7.2, C9.2, C10.2, C11.2, C12.2, C13.2, C14.2, C15.2, C16.2, C17.2, C18.2, C19.2, C20.2, C21.2, C22.2, C23.2, C24.2, C25.2, C26.2, C27.2, C28.2, C29.2, C30.2, C31.2, C32.2, C33.2, C34.2, C35.2, C36.2, C37.2, C38.2, C39.2, C40.2, C41.2, C42.2, C43.2, C44.2, C45.2, C46.2, C47.2, D2.1 (K), D4.2 (A), D7.2 (A), D9.2 (A), D11.2 (A), D13.2 (A), D15.2 (A), D17.2 (A), D19.2 (A), D21.2 (A), D23.2 (A), D25.2 (A), D27.2 (A), D29.2 (A), D31.2 (A), D33.2 (A), D35.2 (A), D37.2 (A), D39.2 (A), D41.2 (A), D43.2 (A), D44.2 (A), D45.2 (A), D46.2 (A), J1.23, J2.1, J3.3, J4.4, J4.5, J4.6, J6.3 (GND), J6.5 (GND), J6.9 (GNDDetect), J7.3 (GND), J7.5 (GND), Q1.2 (E), Q2.2 (E), Q4.2 (E), Q5.2 (E), Q6.2 (E), Q7.2 (E), Q8.2 (E), Q9.2 (E), Q10.2 (E), Q11.2 (E), Q12.2 (E), Q13.2 (E), Q14.2 (E), Q15.2 (E), Q16.2 (E), Q17.2 (E), Q18.2 (E), Q19.2 (E), Q20.2 (E), Q21.2 (E), Q22.2 (E), Q23.1 (E2), Q23.4 (E1), Q24.1 (E2), Q24.4 (E1), Q25.1 (E2), Q25.4 (E1), Q26.1 (E2), Q26.4 (E1), Q27.1 (E2), Q27.4 (E1), Q28.1 (E2), Q28.4 (E1), Q29.1 (E2), Q29.4 (E1), Q30.1 (E2), Q30.4 (E1), Q31.1 (E2), Q31.4 (E1), Q32.1 (E2), Q32.4 (E1), Q33.1 (E2), Q33.4 (E1), Q34.1 (E2), Q34.4 (E1), R2.2, R10.1, R12.1, R17.1, R20.1, R23.1, R26.1, R29.1, R32.1, R35.1, R38.1, R41.1, R44.1, R47.1, R50.1, R53.1, R56.1, R59.1, R62.1, R65.1, R68.1, R71.1, R78.1, R82.1, U1.2 (GND), U1.26 (GND), U1.45 (GND), U1.61 (TST), U1.70 (GND), U1.95 (GND), U2.2 (GND), U3.4 (GND), U4.1 (GNDA), U4.7 (GNDA), U4.10 (GND), U4.16 (GNDA), U4.23 (GND), U4.25 (MOD[0]), U4.26 (MOD[1]), U4.27 (MOD[2]), U4.28 (MOD[3]), U4.46 (GND), Y2.2, Y2.4, Y3.2, Y3.4
unnamed: C44.1, R87.1, R88.1
unnamed: C45.1, R89.1, R90.1
unnamed: D2.2 (A), R3.1
unnamed: D3.1 (K), R8.2
unnamed: D4.1 (K), Q1.1 (B), R9.2, R10.2
unnamed: D5.2 (A), Q3.1 (G), R13.1, R14.2
unnamed: D6.1 (K), R15.2
unnamed: D7.1 (K), Q4.1 (B), R16.2, R17.2
unnamed: D8.1 (K), R18.2
unnamed: D9.1 (K), Q5.1 (B), R19.2, R20.2
unnamed: D10.1 (K), R21.2
unnamed: D11.1 (K), Q6.1 (B), R22.2, R23.2
unnamed: D12.1 (K), R24.2
unnamed: D13.1 (K), Q7.1 (B), R25.2, R26.2
unnamed: D14.1 (K), R27.2
unnamed: D15.1 (K), Q8.1 (B), R28.2, R29.2
unnamed: D16.1 (K), R30.2
unnamed: D17.1 (K), Q9.1 (B), R31.2, R32.2
unnamed: D18.1 (K), R33.2
unnamed: D19.1 (K), Q10.1 (B), R34.2, R35.2
unnamed: D20.1 (K), R36.2
unnamed: D21.1 (K), Q11.1 (B), R37.2, R38.2
unnamed: D22.1 (K), R39.2
unnamed: D23.1 (K), Q12.1 (B), R40.2, R41.2
unnamed: D24.1 (K), R42.2
unnamed: D25.1 (K), Q13.1 (B), R43.2, R44.2
unnamed: D26.1 (K), R45.2
unnamed: D27.1 (K), Q14.1 (B), R46.2, R47.2
unnamed: D28.1 (K), R48.2
unnamed: D29.1 (K), Q15.1 (B), R49.2, R50.2
unnamed: D30.1 (K), R51.2
unnamed: D31.1 (K), Q16.1 (B), R52.2, R53.2
unnamed: D32.1 (K), R54.2
unnamed: D33.1 (K), Q17.1 (B), R55.2, R56.2
unnamed: D34.1 (K), R57.2
unnamed: D35.1 (K), Q18.1 (B), R58.2, R59.2
unnamed: D36.1 (K), R60.2
unnamed: D37.1 (K), Q19.1 (B), R61.2, R62.2
unnamed: D38.1 (K), R63.2
unnamed: D39.1 (K), Q20.1 (B), R64.2, R65.2
unnamed: D40.1 (K), R66.2
unnamed: D41.1 (K), Q21.1 (B), R67.2, R68.2
unnamed: D42.1 (K), R69.2
unnamed: D43.1 (K), Q22.1 (B), R70.2, R71.2
unnamed: D44.1 (K), R72.2, R74.1
unnamed: D45.1 (K), R73.2, R75.1
unnamed: D47.1 (K), RN3.1 (R1.1)
unnamed: D48.1 (K), RN4.1 (R1.1)
unnamed: D49.1 (K), RN5.1 (R1.1)
unnamed: D50.1 (K), RN3.2 (R2.1)
unnamed: D51.1 (K), RN4.2 (R2.1)
unnamed: D52.1 (K), RN5.2 (R2.1)
unnamed: D53.1 (K), RN3.3 (R3.1)
unnamed: D54.1 (K), RN4.3 (R3.1)
unnamed: D55.1 (K), RN5.3 (R3.1)
unnamed: D56.1 (K), RN3.4 (R4.1)
unnamed: D57.1 (K), RN4.4 (R4.1)
unnamed: D58.1 (K), RN5.4 (R4.1)
unnamed: D59.1 (K), RN6.1 (R1.1)
unnamed: D60.1 (K), RN7.1 (R1.1)
unnamed: D61.1 (K), RN8.1 (R1.1)
unnamed: D62.1 (K), RN6.2 (R2.1)
unnamed: D63.1 (K), RN7.2 (R2.1)
unnamed: D64.1 (K), RN8.2 (R2.1)
unnamed: D65.1 (K), RN6.3 (R3.1)
unnamed: D66.1 (K), RN7.3 (R3.1)
unnamed: D67.1 (K), RN8.3 (R3.1)
unnamed: D68.1 (K), RN6.4 (R4.1)
unnamed: D69.1 (K), RN7.4 (R4.1)
unnamed: D70.1 (K), RN8.4 (R4.1)
unnamed: J5.10, R91.2
unnamed: J5.12, R92.2
unnamed: C47.1, J5.8 (SHIELD)
unnamed: Q2.1 (B), R11.1, R12.2
unnamed: Q2.3 (C), R14.1
unnamed: Q23.3 (C1), RN3.8 (R1.2)
unnamed: Q23.6 (C2), RN3.7 (R2.2)
unnamed: Q24.3 (C1), RN4.8 (R1.2)
unnamed: Q24.6 (C2), RN4.7 (R2.2)
unnamed: Q25.3 (C1), RN5.8 (R1.2)
unnamed: Q25.6 (C2), RN5.7 (R2.2)
unnamed: Q26.3 (C1), RN3.6 (R3.2)
unnamed: Q26.6 (C2), RN3.5 (R4.2)
unnamed: Q27.3 (C1), RN4.6 (R3.2)
unnamed: Q27.6 (C2), RN4.5 (R4.2)
unnamed: Q28.3 (C1), RN5.6 (R3.2)
unnamed: Q28.6 (C2), RN5.5 (R4.2)
unnamed: Q29.3 (C1), RN6.8 (R1.2)
unnamed: Q29.6 (C2), RN6.7 (R2.2)
unnamed: Q30.3 (C1), RN7.8 (R1.2)
unnamed: Q30.6 (C2), RN7.7 (R2.2)
unnamed: Q31.3 (C1), RN8.8 (R1.2)
unnamed: Q31.6 (C2), RN8.7 (R2.2)
unnamed: Q32.3 (C1), RN6.6 (R3.2)
unnamed: Q32.6 (C2), RN6.5 (R4.2)
unnamed: Q33.3 (C1), RN7.6 (R3.2)
unnamed: Q33.6 (C2), RN7.5 (R4.2)
unnamed: Q34.3 (C1), RN8.6 (R3.2)
unnamed: Q34.6 (C2), RN8.5 (R4.2)
unnamed: R81.1, R82.2
unnamed: C8.1, U2.1 (CB)
unnamed: R77.1, R78.2, U2.3 (FB)
unnamed: R76.1, U2.4 (~SHDN)
unnamed: R81.2, U4.9 (RSET_BG)
unnamed: R86.2, U4.5 (RXIN)
unnamed: R85.2, U4.6 (RXIP)
unnamed: R84.2, U4.2 (TXON)
unnamed: R83.2, U4.3 (TXOP)
unnamed: C36.1, R79.1, U4.12 (XSCI), Y3.3
unnamed: C33.1, R79.2, U4.11 (XSCO), Y3.1
